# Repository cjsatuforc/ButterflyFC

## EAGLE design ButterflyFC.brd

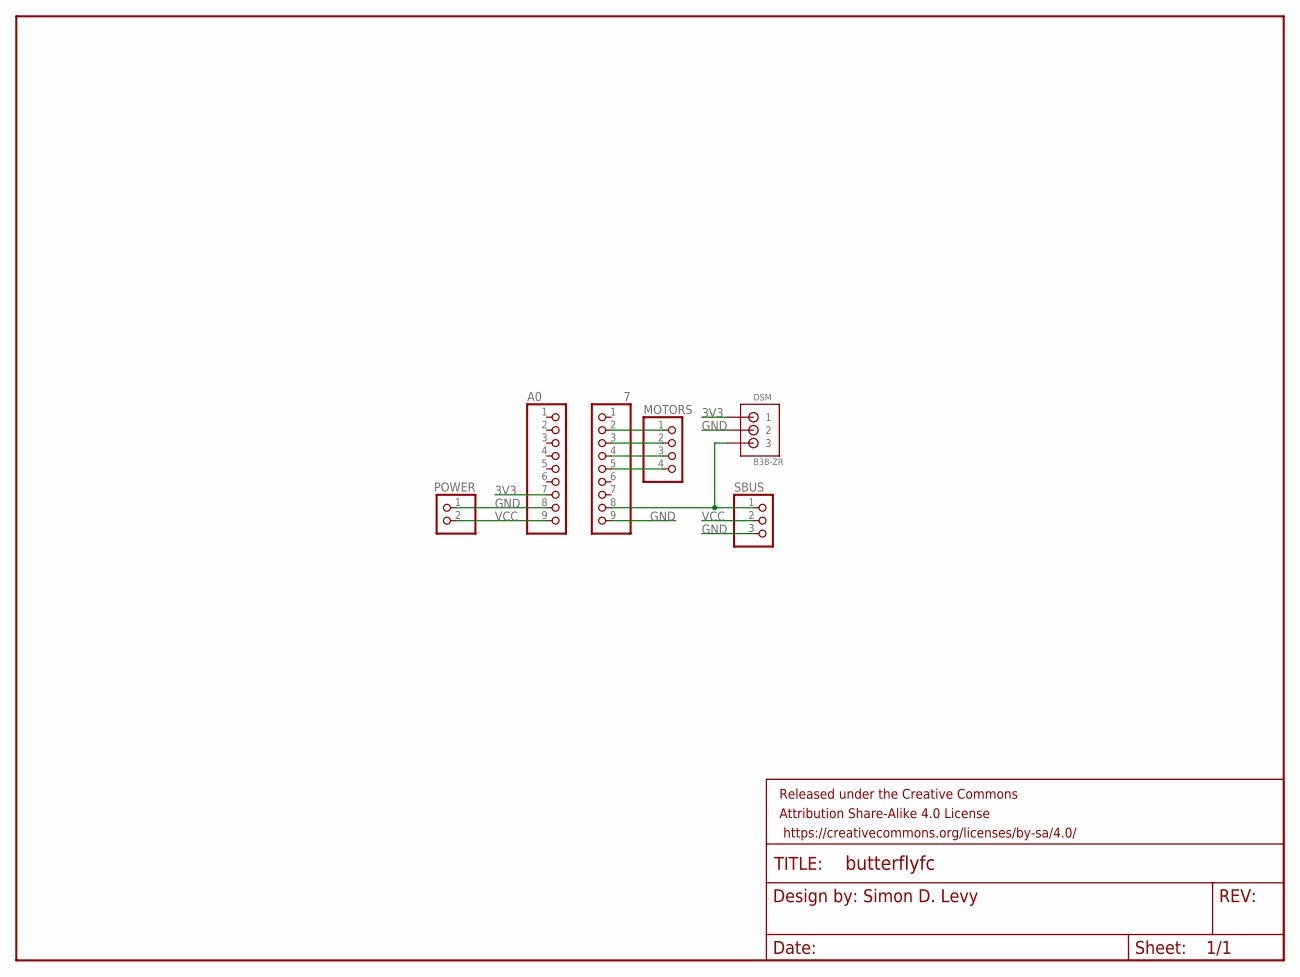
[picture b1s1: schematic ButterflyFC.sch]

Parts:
7: PINHD-1X9; 1X09
A0: PINHD-1X9; 1X09
DSM: B3B-ZR
FRAME1: FRAME-LETTER; CREATIVE_COMMONS
MOTORS: PINHD-1X4; 1X04
POWER: PINHD-1X2; 1X02
SBUS: PINHD-1X3; 1X03

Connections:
3V3: A0.7, DSM.1
GND: 7.9, A0.8, DSM.2, POWER.1, SBUS.3
M1: 7.5, MOTORS.4
M2: 7.4, MOTORS.3
M3: 7.3, MOTORS.2
M4: 7.2, MOTORS.1
RX1: 7.8, DSM.3, SBUS.1
VCC: A0.9, POWER.2, SBUS.2

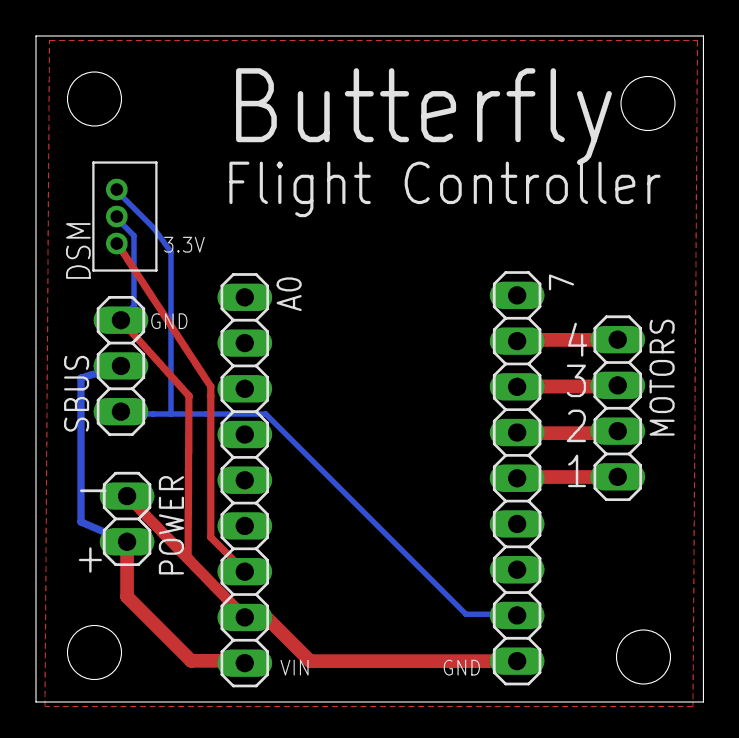
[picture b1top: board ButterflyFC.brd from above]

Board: 2 copper layers, 37.1 x 37.0 mm, 7 parts (0 on the bottom side), 8 nets.

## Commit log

2018-04-21 Added ESC power rail
2018-04-21 Begin board
2018-04-21 Routed board
2018-04-21 Added copper pour, moutning holes
2018-04-21 Fixed borked .brd file
2018-04-21 Restoring copper pour
2018-04-21 Copper pour restored
2018-04-21 Fixed broken 3.3V connection
2018-04-22 Added stencil, bigger holes
2018-04-22 Cleanup
2018-04-22 Aligned holes
2018-04-22 Added designer name
2018-04-22 Added labels for Butterfly pinout
2018-04-22 Corrected labels on top pins
2018-04-22 Goosed-up power-wire widths
2018-04-22 Fixed GND trace on power-in
2018-04-22 Rebuild board
2018-04-22 Re-routed board
2018-04-22 Ground pour, ERC
2018-04-22 Begin silkscreening
2018-04-22 More silkscreen
2018-04-23 Aligned / expaneded mounting holes
2018-04-23 Adjusted Butterfly board mounting hole positions
2018-04-24 Added silkscreen for logo

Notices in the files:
parts and their libraries:
SparkFun-Aesthetics: Licensing: Creative Commons ShareAlike 4.0 International - https://creativecommons.org/licenses/by-sa/4.0
SparkFun-Aesthetics: Released under the Creative Commons Attribution Share-Alike 4.0 License
SparkFun-Aesthetics: https://creativecommons.org/licenses/by-sa/4.0
